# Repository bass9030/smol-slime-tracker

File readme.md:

# smol-slime-track

Smol body tracker for slimevr

> [!CAUTION]
> This PCB is not tested at real hardware yet. It may not work. We do not recommend using this PCB to build a slime VR tracker.

> [!WARNING]
> I'm not good at PCB Design and I'm also not expert about PCB Design & Electronic circuit. This circuit may have potential danger(circuit shorts, wrong pin connection, etc). It passed ERC & DRC, but If using this PCB Design. Please check again if something wrong.

# Specification

-   PCB Size: 37.9mm x 34.9mm 4-Layer PCB
-   MCU: ESP32-C3-WROOM-02
-   IMU: ICM-45686
-   Charge IC: MCP73871(Charge) + DW01A(Overcharge & Overdischarge Protection)

# Images

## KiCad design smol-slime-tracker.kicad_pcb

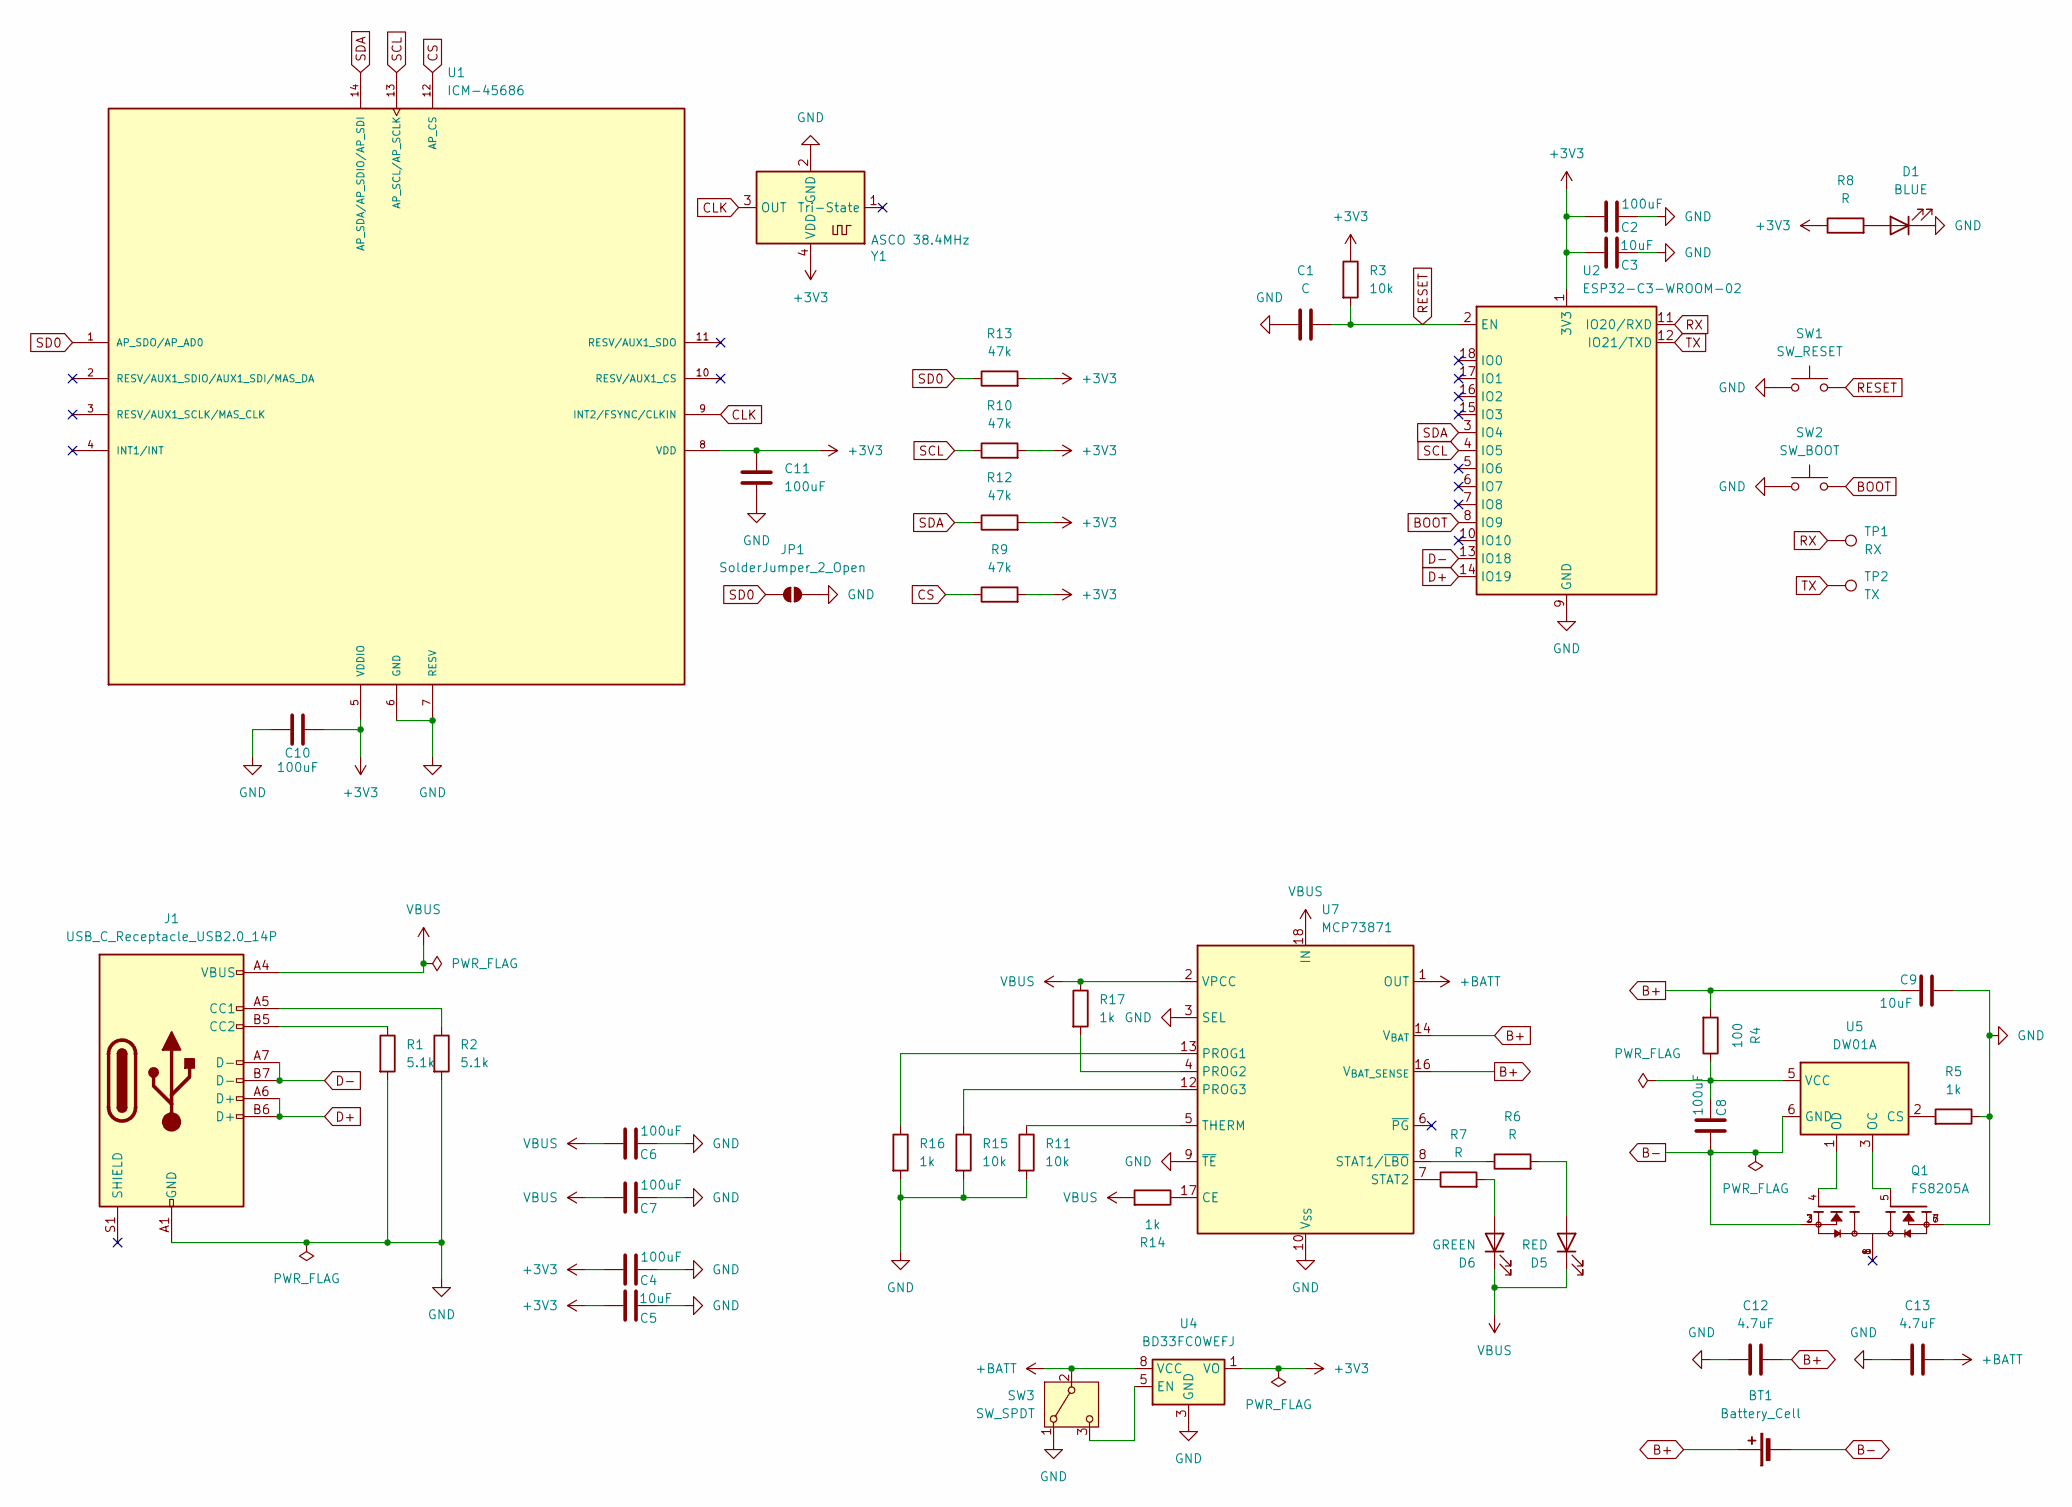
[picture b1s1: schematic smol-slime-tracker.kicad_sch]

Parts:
BT1: Battery_Cell; JST_PH_B2B-PH-K_1x02_P2.00mm_Vertical
C1: C; C_0603_1608Metric
C2, C4, C6, C7, C8, C10, C11: 100uF; C_0603_1608Metric
C3, C5, C9: 10uF; C_0603_1608Metric
C12, C13: 4.7uF; C_0603_1608Metric
D1: BLUE; LED_0603_1608Metric
D5: RED; LED_0603_1608Metric
D6: GREEN; LED_0603_1608Metric
J1: USB_C_Receptacle_USB2.0_14P; USB_C_Receptacle_GCT_USB4105-xx-A_16P_TopMnt_Horizontal
JP1: SolderJumper_2_Open; SolderJumper-2_P1.3mm_Open_RoundedPad1.0x1.5mm
Q1: FS8205A; PARTREV 1.7
R1, R2: 5.1k; R_0603_1608Metric
R3, R11, R15: 10k; R_0603_1608Metric
R4: 100; R_0603_1608Metric
R5, R14, R16, R17: 1k; R_0603_1608Metric
R6, R7, R8: R; R_0603_1608Metric
R9, R10, R12, R13: 47k; R_0603_1608Metric
SW1: SW_RESET; SW_Push_1P1T_NO_CK_KMR2
SW2: SW_BOOT; SW_Push_1P1T_NO_CK_KMR2
SW3: SW_SPDT; SW_SPDT_CK_JS102011SAQN
TP1: RX; TestPoint_Pad_D1.0mm
TP2: TX; TestPoint_Pad_D1.0mm
U1: ICM-45686; IC_ICM-45686; PARTREV 0.2
U2: ESP32-C3-WROOM-02
U4: BD33FC0WEFJ; HTSOP-8-1EP_3.9x4.9mm_P1.27mm_EP2.4x3.2mm
U5: DW01A; SOT-23-6
U7: MCP73871; QFN-20-1EP_4x4mm_P0.5mm_EP2.5x2.5mm
Y1: ASCO 38.4MHz; Oscillator_SMD_Abracon_ASCO-4Pin_1.6x1.2mm

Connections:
+3V3: C2.1, C3.1, C4.1, C5.1, C10.2, C11.1, R3.1, R8.1, R9.2, R10.2, R12.2, R13.2, U1.5 (VDDIO), U1.8 (VDD), U2.1 (3V3), U4.1 (VO), Y1.4 (VDD)
+BATT: C13.2, SW3.2 (B), U4.8 (VCC), U7.1 (OUT), U7.20 (OUT)
B+: BT1.1 (+), C9.2, C12.2, R4.2, U7.14 (V_{BAT}), U7.15 (V_{BAT}), U7.16 (V_{BAT_SENSE})
B-: BT1.2 (-), C8.1, Q1.2, Q1.3, U5.6 (GND)
BOOT: SW2.2, U2.8 (IO9)
CLK: U1.9 (INT2/FSYNC/CLKIN), Y1.3 (OUT)
CS: R9.1, U1.12 (AP_CS)
D+: J1.A6 (D+), J1.B6 (D+), U2.14 (IO19)
D-: J1.A7 (D-), J1.B7 (D-), U2.13 (IO18)
GND: C1.1, C2.2, C3.2, C4.2, C5.2, C6.2, C7.2, C9.1, C10.1, C11.2, C12.1, C13.1, D1.1 (K), J1.A1 (GND), J1.A12 (GND), J1.B1 (GND), J1.B12 (GND), JP1.2 (B), Q1.6, Q1.7, R1.2, R2.2, R5.1, R11.2, R15.2, R16.2, SW1.1, SW2.1, SW3.1 (A), U1.6 (GND), U1.7 (RESV), U2.9 (GND), U2.19 (GND), U4.3 (GND), U4.9 (GND), U7.3 (SEL), U7.9 (~TE), U7.10 (V_{SS}), U7.11 (V_{SS}), U7.21 (V_{SS}), Y1.2 (GND)
unnamed: D1.2 (A), R8.2
unnamed: D5.2 (A), R6.2
unnamed: D6.2 (A), R7.2
unnamed: J1.A5 (CC1), R2.1
unnamed: J1.B5 (CC2), R1.1
unnamed: SW3.3 (C), U4.5 (EN)
unnamed: R5.2, U5.2 (CS)
unnamed: Q1.5, U5.3 (OC)
unnamed: Q1.4, U5.1 (OD)
unnamed: C8.2, R4.1, U5.5 (VCC)
unnamed: R14.1, U7.17 (CE)
unnamed: R16.1, U7.13 (PROG1)
unnamed: R17.2, U7.4 (PROG2)
unnamed: R15.1, U7.12 (PROG3)
unnamed: R6.1, U7.8 (STAT1/~LBO)
unnamed: R7.1, U7.7 (STAT2)
unnamed: R11.1, U7.5 (THERM)
RESET: C1.2, R3.2, SW1.2, U2.2 (EN)
RX: TP1.1, U2.11 (IO20/RXD)
SCL: R10.1, U1.13 (AP_SCL/AP_SCLK), U2.4 (IO5)
SD0: JP1.1 (A), R13.1, U1.1 (AP_SDO/AP_AD0)
SDA: R12.1, U1.14 (AP_SDA/AP_SDIO/AP_SDI), U2.3 (IO4)
TX: TP2.1, U2.12 (IO21/TXD)
VBUS: C6.1, C7.1, D5.1 (K), D6.1 (K), J1.A4 (VBUS), J1.A9 (VBUS), J1.B4 (VBUS), J1.B9 (VBUS), R14.2, R17.1, U7.2 (VPCC), U7.18 (IN), U7.19 (IN)

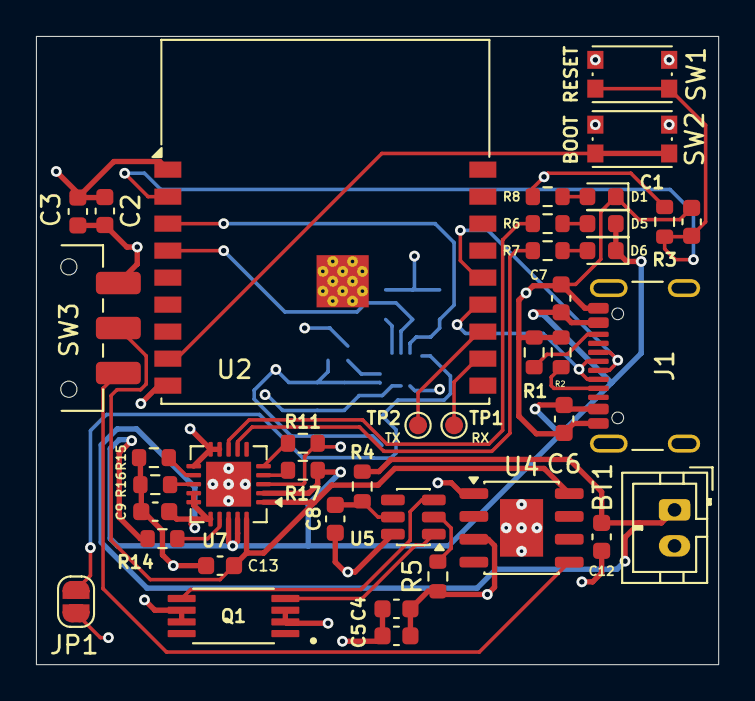
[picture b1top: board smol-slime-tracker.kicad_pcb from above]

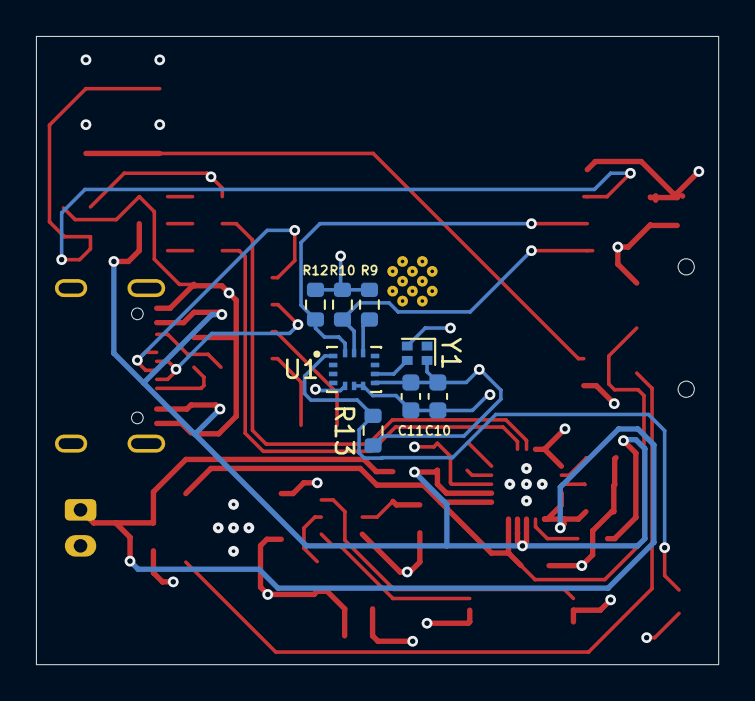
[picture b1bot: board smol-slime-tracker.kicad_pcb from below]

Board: 4 copper layers, 37.9 x 34.9 mm, 48 parts (8 on the bottom side), 34 nets.

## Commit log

2025-10-21 Add images
2025-10-21 Add readme.md
2025-10-21 Edit readme.md
2025-10-21 Edit readme again
2025-10-21 renamed some header
